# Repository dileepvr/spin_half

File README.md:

This board design, as well as course teaching materials and avr-gcc
code are being released under the GPL_v3 license. All future versions
of GPL automatically apply.

Written by Dileep V. Reddy on March 6th, 2014.

This simple board is meant to aid in teaching Quantum Key Distribution
via polarized photons (BB84 protocol) using an interactive in-class
activity. This was first designed for and deployed at a pilot course
titled "Quantum Mechanics for Everyone" under the aegis of the Science
Literacy Program (SPL) at the University of Oregon.

The board PCB layout files are zipped in the gerber folder, and may be
uploaded to any online PCB printing service (such as OSHPark).  The
code meant to run on the attiny2313 microcontroller is presend inside
the avr_code folder, along with a Makefile. Use avr-gcc and avrdude to
compile and upload to the board.

Refer to files "spin_half_doc.pdf" and "qkd_handout.pdf" for more
information.

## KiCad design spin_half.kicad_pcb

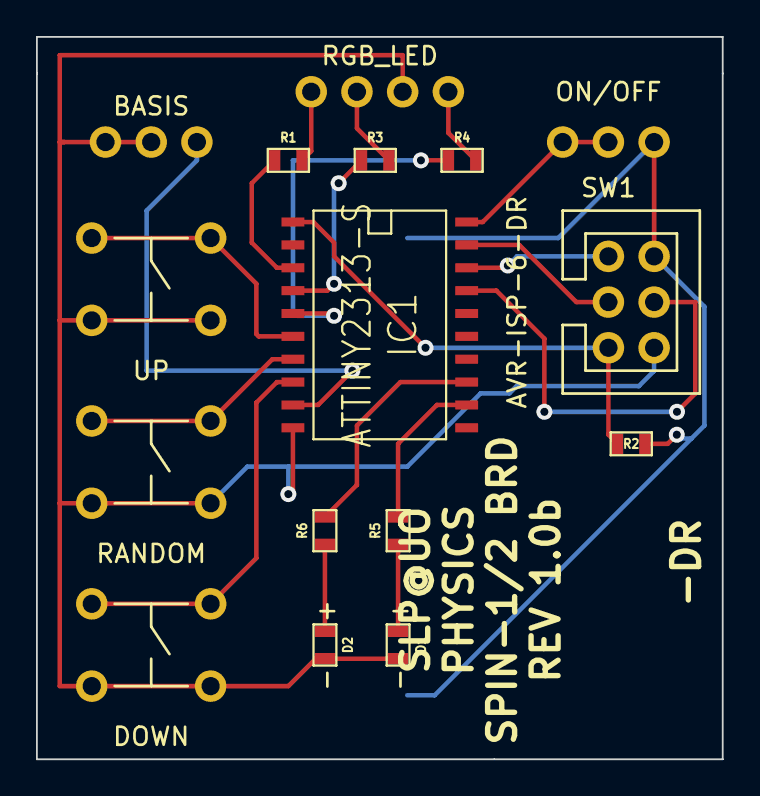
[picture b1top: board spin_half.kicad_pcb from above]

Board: 2 copper layers, 38.1 x 40.1 mm, 17 parts (1 on the bottom side), 21 nets.

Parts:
BT1: BATTERY; CR2032
CON1: AVR-ISP-6-DR
D1, D2: LED; SM0603_DR
IC1: ATTINY2313-S; SO20L
R1, R3, R4, R5, R6: 200; SM0603
R2: 1K; SM0603
RGBL1: RGB_LED
SW1: ON/OFF; SW_SPDT_DR
SW2: BASIS; SW_SPDT_DR
SW3: DOWN; SW_TACT
SW4: RANDOM; SW_TACT
SW5: UP; SW_TACT

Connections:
/MOSI: CON1.4, IC1.17
/PD1: IC1.3, R1.1
/RST: CON1.5, IC1.1, R2.2
GND: BT1.2, CON1.6, D1.2, D2.2, IC1.10, RGBL1.2, SW2.2, SW3.2, SW4.2, SW5.2
unnamed: IC1.9, SW2.1
unnamed: IC1.8, SW3.1
unnamed: IC1.7, SW4.1
unnamed: IC1.5, R4.1
unnamed: CON1.1, IC1.18
unnamed: CON1.3, IC1.19
unnamed: R4.2, RGBL1.1
unnamed: IC1.4, R3.1
unnamed: R3.2, RGBL1.3
unnamed: R1.2, RGBL1.4
unnamed: IC1.12, R5.2
unnamed: D2.1, R6.1
unnamed: D1.1, R5.1
unnamed: IC1.13, R6.2
unnamed: IC1.6, SW5.1
unnamed: IC1.20, SW1.2
VCC: BT1.1, CON1.2, R2.1, SW1.1

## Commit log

2016-07-30 kicad and avr code in.
2016-07-31 Added schematic pdf.
